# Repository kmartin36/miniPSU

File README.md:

miniPSU
=======

Small linear power supply with adjustable voltage and current

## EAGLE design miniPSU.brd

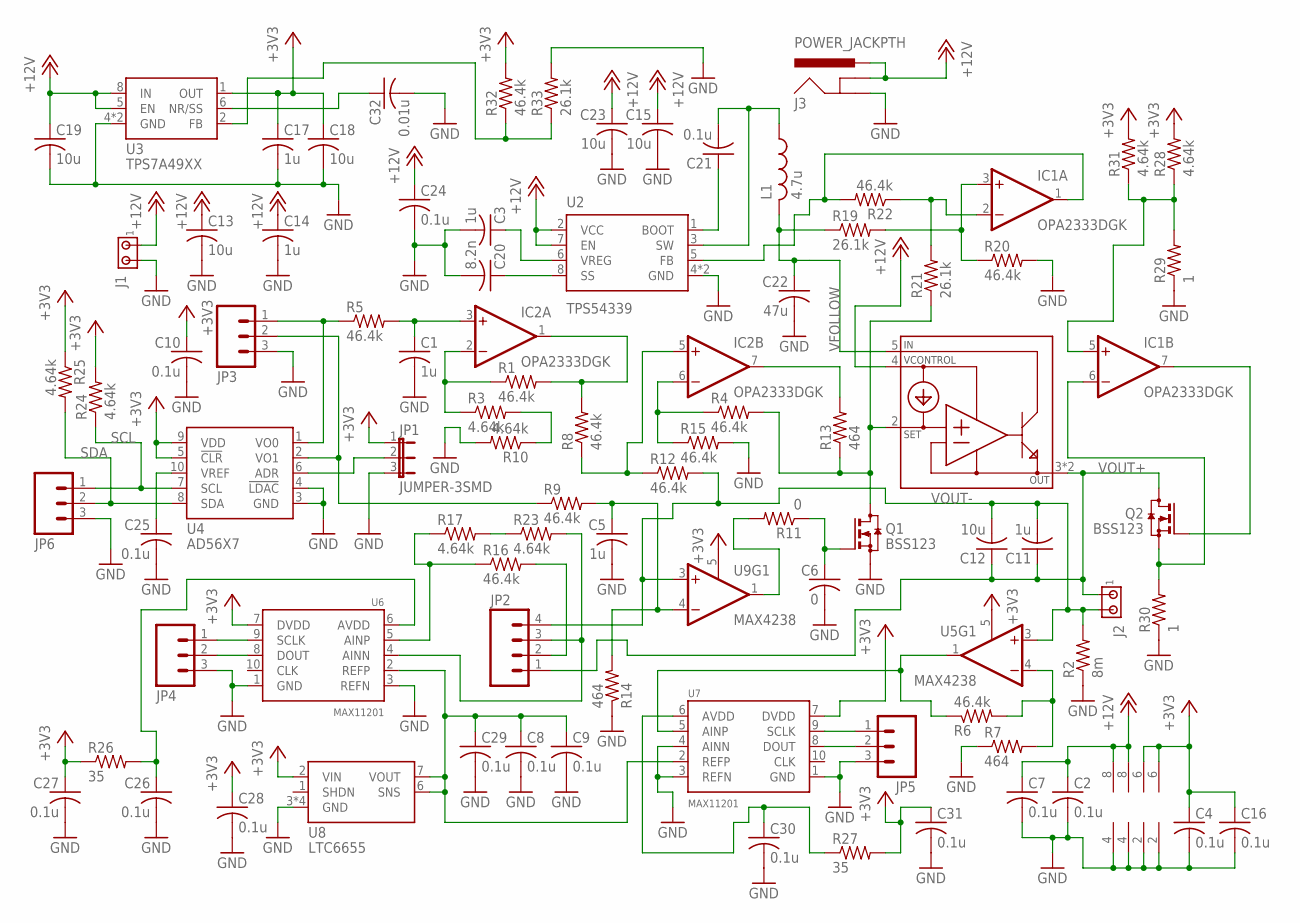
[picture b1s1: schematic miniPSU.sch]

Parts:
C1, C3, C5, C11, C14, C17: 1u; C0603
C2, C4, C7, C8, C9, C10, C16, C21, C24, C25, C26, C27, C28, C29, C30, C31: 0.1u; C0603
C6: 0; C0603
C12, C13, C15, C18, C19, C23: 10u; C1206
C20: 8.2n; C0603
C22: 47u; C1210
C32: 0.01u; C0603
IC1, IC2: OPA2333DGK; MSOP08
J1, J2: MTA02-156; 1X2MTA
J3: POWER_JACKPTH; POWER_JACK_PTH
JP1: JUMPER-3SMD; SJ_3
JP2: M04LOCK; 1X04_LOCK
JP3, JP4, JP5, JP6: M03LOCK; 1X03_LOCK
L1: 4.7u; XAL4000
Q1, Q2: BSS123; SOT23
R1, R4, R5, R6, R8, R9, R12, R15, R16, R20, R22, R32: 46.4k; C0603
R2: 8m; C1206
R3, R10, R17, R23, R24, R25, R28, R31: 4.64k; C0603
R7, R13, R14: 464; C0603
R11: 0; C0603
R19, R21, R33: 26.1k; C0603
R26, R27: 35; C0603
R29, R30: 1; C0603
U1: LT3083-Q; D2PAK-5
U2: TPS54339; SO-08-PAD
U3: TPS7A49XX; MSOP-8
U4: AD56X7; S-PDSO-G10
U5, U9: MAX4238; SOT23-6
U6, U7: MAX11201; S-PDSO-G10
U8: LTC6655; MSOP-8-NOPAD

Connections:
+3V3: C4.1, C10.1, C16.1, C17.1, C18.1, C27.1, C28.1, C31.1, JP1.1, R24.2, R25.1, R26.1, R27.2, R28.2, R31.2, R32.2, U3.1 (OUT), U4.5 (!CLR), U4.9 (VDD), U5.5 (EN), U5.6 (V+), U6.7 (DVDD), U7.7 (DVDD), U8.2 (VIN), U9.5 (EN), U9.6 (V+)
+12V: C2.1, C7.1, C13.1, C14.1, C15.1, C19.1, C23.1, C24.1, IC1.8 (V+), IC2.8 (V+), J1.1, J3.GNDBREAK, J3.PWR, U1.4 (VCONTROL), U2.2 (VCC), U2.7 (EN), U3.5 (EN), U3.8 (IN)
GND: C1.2, C2.2, C3.2, C4.2, C5.2, C6.2, C7.2, C8.2, C9.2, C10.2, C13.2, C14.2, C15.2, C16.2, C17.2, C18.2, C19.2, C20.2, C22.2, C23.2, C24.2, C25.2, C26.2, C27.2, C28.2, C29.2, C30.2, C31.2, C32.2, IC1.4 (V-), IC2.4 (V-), J1.2, J3.GND, JP1.3, JP3.3, JP4.3, JP5.3, JP6.3, Q1.2 (S), R2.1, R7.1, R10.2, R14.1, R15.2, R20.2, R29.1, R30.1, R33.2, U2.4 (GND), U2.PAD (GND), U3.4 (GND), U3.TH (GND), U4.3 (GND), U4.4 (!LDAC), U5.2 (V-), U6.1 (GND), U6.3 (REFN), U7.1 (GND), U7.3 (REFN), U7.4 (AINN), U8.3 (GND), U8.4 (GND), U8.5 (GND), U8.8 (GND), U9.2 (V-)
unnamed: C32.1, U3.6 (NR/SS)
unnamed: C26.1, R26.2, U6.6 (AVDD)
unnamed: C1.1, IC2.3 (+IN), R5.2
unnamed: R6.2, R7.2, U5.4 (-IN)
unnamed: R6.1, U5.1 (OUT), U7.5 (AINP)
unnamed: C5.1, R9.2, R14.2, U9.4 (-IN)
unnamed: R11.2, U9.1 (OUT)
unnamed: Q1.3 (D), R4.2, R13.1, R21.1, U1.2 (SET)
unnamed: IC2.2 (-IN), R1.1, R3.1
unnamed: IC2.7 (OUT), R13.2
unnamed: IC2.1 (OUT), R1.2, R8.2
unnamed: IC2.5 (+IN), R8.1, R12.1
unnamed: IC2.6 (-IN), R4.1, R15.1
unnamed: C3.1, U2.6 (VREG)
unnamed: JP3.1, R5.1, U4.1 (VO0)
unnamed: JP3.2, R9.1, U4.2 (VO1)
unnamed: C20.1, U2.8 (SS)
unnamed: C6.1, Q1.1 (G), R11.1
unnamed: C30.1, R27.1, U7.6 (AVDD)
unnamed: IC1.1 (OUT), R22.2, U2.5 (FB)
unnamed: IC1.3 (+IN), R19.2, R20.1
unnamed: IC1.2 (-IN), R21.2, R22.1
unnamed: JP1.2, U4.6 (ADR)
unnamed: C25.1, U4.10 (VREF)
unnamed: R3.2, R10.1
unnamed: R17.2, R23.1
unnamed: IC1.7 (OUT), Q2.1 (G)
unnamed: R16.1, R17.1, U6.5 (AINP)
unnamed: IC1.5 (+IN), R28.1, R29.2, R31.1
unnamed: IC1.6 (-IN), Q2.2 (S), R30.2
unnamed: C21.1, U2.1 (BOOT)
unnamed: C21.2, L1.P$1 (1), U2.3 (SW)
unnamed: JP2.2, R16.2
unnamed: JP2.3, R23.2, U6.4 (AINN)
unnamed: JP4.2, U6.8 (DOUT)
unnamed: C8.1, C9.1, C29.1, U6.2 (REFP), U7.2 (REFP), U8.6 (SNS), U8.7 (VOUT)
unnamed: JP4.1, U6.9 (SCLK)
unnamed: JP5.2, U7.8 (DOUT)
unnamed: JP5.1, U7.9 (SCLK)
unnamed: R32.1, R33.1, U3.2 (FB)
SCL: JP6.1, R24.1, U4.7 (SCL)
SDA: JP6.2, R25.2, U4.8 (SDA)
VFOLLOW: C22.1, L1.P$2 (2), R19.1, U1.5 (IN)
VOUT+: C11.1, C12.1, J2.1, JP2.1, Q2.3 (D), U1.3 (OUT), U1.PAD (OUT)
VOUT-: C11.2, C12.2, J2.2, JP2.4, R2.2, R12.2, U5.3 (+IN), U9.3 (+IN)

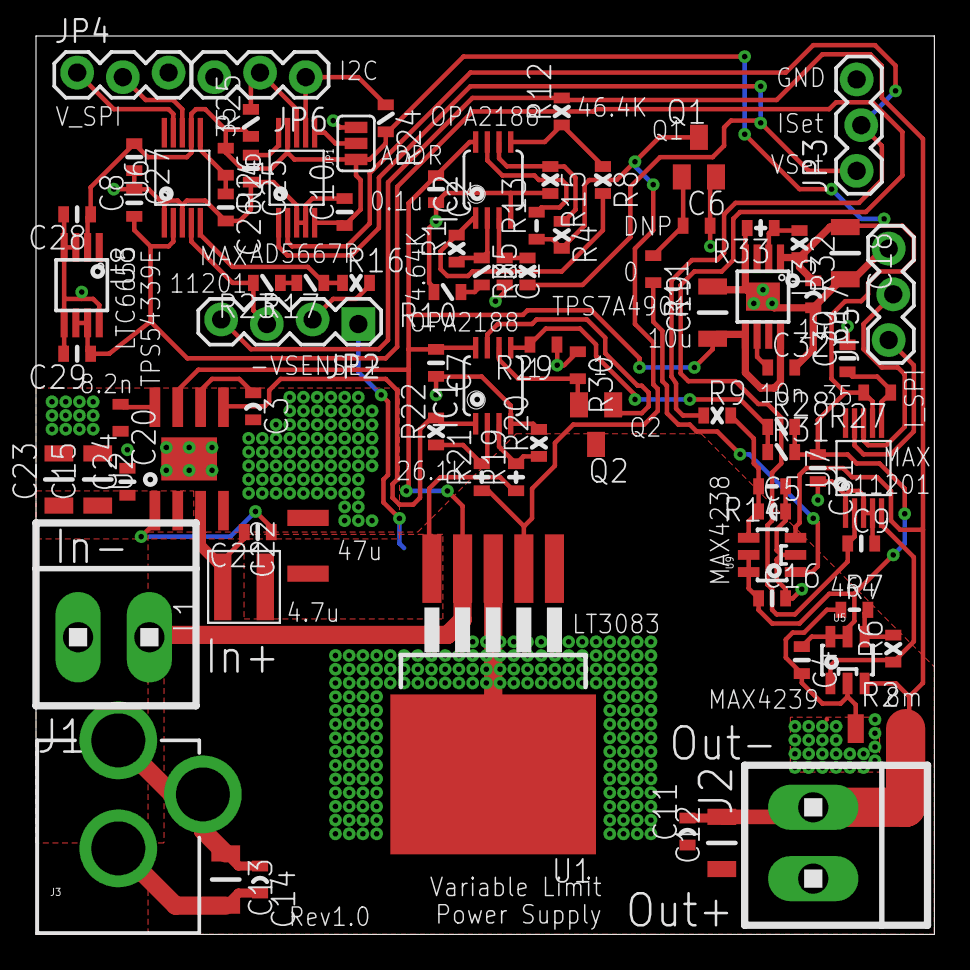
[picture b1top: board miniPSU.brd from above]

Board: 2 copper layers, 49.9 x 49.9 mm, 87 parts (0 on the bottom side), 48 nets.

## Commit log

2014-10-18 Renaming files
2014-10-19 Moving to higher resolution ADC and DAC
2014-10-20 Initial placement
2014-10-20 Corrected voltage reference package
2014-10-20 Changed bias current opamp Added i2c connector
2014-10-20 Changed to low noise 3v3 regulator Put resistors between ADCs' AVDD and DVDD
2014-10-20 Changed switching converter to an easier to solder package Changed resistor values to reduce the number of needed values
2014-10-20 Beginning routing
2014-10-22 Initial routing done
2014-10-26 Routing improvements
2014-10-26 Shortened current feedback loop
2014-10-26 Added more thermal vias
2014-11-07 Added thermal vias under the switching regulator to help with soldering
2014-11-07 Simplified a few values Added silkscreen
2014-11-07 Silkscreen improvements Placement tweaks

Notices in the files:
parts and their libraries:
SparkFun-Connectors: Licensing: CC v3.0 Share-Alike You are welcome to use this library for commercial purposes.
